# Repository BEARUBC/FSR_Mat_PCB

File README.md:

# FSR Matrix Printed Circuit Board

**As of 2023-03-24, this README is outdated. Documentation for Tiaan's FSR is in progress. 

<p align="center">
These are the CAD files for the FSR printed circuit boards (PCB) using through-hole only components. This board is used for controlling a force sensitive resistor matrix, reading analog values from each cell.  
</p>

## 📖 Description

This design is based off of Sensitronics' MatrixArray products which are comprised of a multitude of force sensing resistor elements arranged in a grid.
Providing n-input multitouch + force sensing capabilities, MatrixArrays are the basis for musical instruments, PC input devices, and other innovative designs.
If you have measured single-element FSRs by looking at the voltage across a divider, we're doing the same thing here.

But in this case, we're choosing the point to measure by powering a single drive column, enabling one mux channel so that the ADC sees a single row.
In the next section, the Arduino code demonstrates a scan pattern to read all $\approx$ 160 elements in sequence.

### 🚨 Dependencies

* Software
  * KiCAD v6
* Hardware
  * ThruMode MatrixArray
  * Arduino Uno (or other)
  * 74HC595 Shift Register (x2)
  * 74HC4051 Analog Multiplexer (x2)
  * 20k resistor (x1)
  * Solderless Breadboard & Jumper Wire

### 💻 Installing

#### 🕹️ Software

Use a web browser to navigate to www.kicad.org the KiCad EDA website. Click the DOWNLOAD button on the KiCad home page. On the download page that opens, click the Windows button. Under Stable Release, click either Windows 64-bit or Windows 32-bit, depending on if you are going to install KiCad on a 32-bit or 64-bit version of the Windows operating system. Save the KiCad installation file. It may take a while to download, depending on your internet speed.

1. Click the Open button under File > Open (`Ctrl + O`) and navigate to this repository
2. Select the `force_sens_resistor.kicad_pro` file
3. Double click the `*.sch` file and begin to edit the board

#### 🤖 Hardware

Arrange the hardware connections folling this schematic:

### ▶️ Executing program

Now that the hardware's connected, it's time to write some code.

To read a single intersection, or "cell", of the MatrixArray, we need to perform the following sequence:

* Drive the cell's row with +5V
* Enable the cell's column (multiplexer channel)
* Take an ADC reading on pin A0
* Output the reading via serial port

Simple enough, so from here, we will write a scan pattern to efficiently drive and read each cell of the Matrix. Recalling that we're calling shift register drive pins "rows" and multiplexed read pins "columns" in this example, we'll enable each column in order, and while each column is active, we'll drive each row high and take a reading.

```cpp
// Constant definitions
...

void setup() {
  Serial.begin(BAUD_RATE);

  pinMode(PIN_ADC_INPUT, INPUT);
  pinMode(PIN_SHIFT_REGISTER_DATA, OUTPUT);
  pinMode(PIN_SHIFT_REGISTER_CLOCK, OUTPUT);
  pinMode(PIN_MUX_CHANNEL_0, OUTPUT);
  pinMode(PIN_MUX_CHANNEL_1, OUTPUT);
  pinMode(PIN_MUX_CHANNEL_2, OUTPUT);
  pinMode(PIN_MUX_INHIBIT_0, OUTPUT);
  pinMode(PIN_MUX_INHIBIT_1, OUTPUT);
}
void loop() {
  for(int i = 0; i < ROW_COUNT; i ++) {
    setRow(i);
    shiftColumn(true);
    shiftColumn(false);                         //with SR clks tied, latched outputs are one clock behind

    for(int j = 0; j < COLUMN_COUNT; j ++) {
      int raw_reading = analogRead(PIN_ADC_INPUT);
      byte send_reading = (byte) (lowByte(raw_reading >> 2));
      shiftColumn(false);
      printFixed(send_reading);
      Serial.print(" ");
    }
    Serial.println();
  }
  Serial.println();
  delay(200);
}

...

// Function implementations for `setRow`, `shiftCoumn`, and `printFixed`

```

## 🧔🏽‍♂️Authors

Contributors names and contact info

Tiaan Boshoff
Kyle Kochi
Tiffany Prayitino
Umar Ali  

## 🧾 Version History

* 1.0
    * Initial Release following Sensitronics' MatrixArray tutorial

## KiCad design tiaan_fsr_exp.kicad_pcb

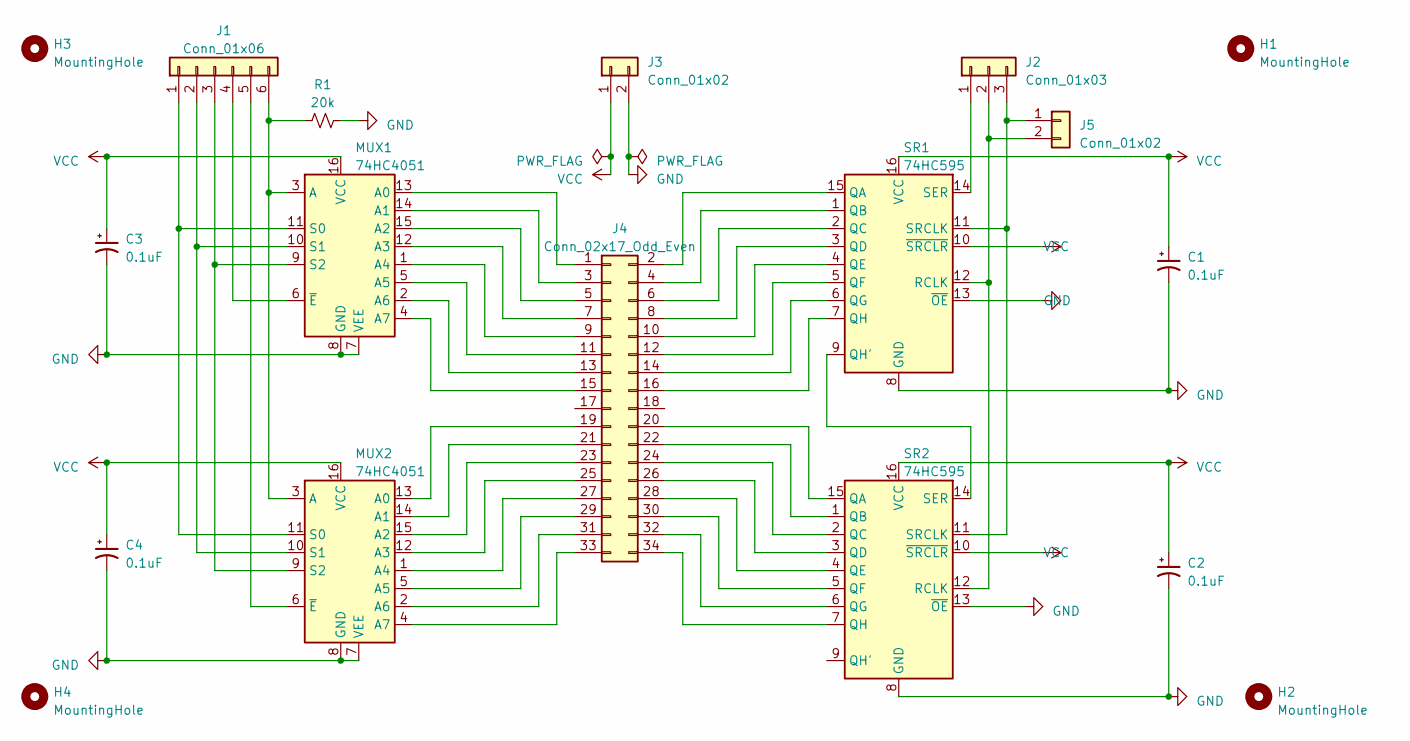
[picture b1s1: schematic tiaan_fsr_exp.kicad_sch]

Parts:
C1, C2, C3, C4: 0.1uF; CP_Radial_D4.0mm_P2.00mm
H1, H2, H3, H4: MountingHole; MountingHole_2.7mm_M2.5_DIN965_Pad
J1: Conn_01x06; JST_XH_S6B-XH-A-1_1x06_P2.50mm_Horizontal
J2: Conn_01x03; JST_XH_S3B-XH-A-1_1x03_P2.50mm_Horizontal
J3, J5: Conn_01x02; PinHeader_1x02_P2.54mm_Vertical
J4: Conn_02x17_Odd_Even; IDC-Header_2x17_P2.54mm_Vertical
MUX1, MUX2: 74HC4051; DIP-16_W7.62mm_Socket
R1: 20k; R_Axial_DIN0207_L6.3mm_D2.5mm_P10.16mm_Horizontal
SR1, SR2: 74HC595; DIP-16_W7.62mm_Socket

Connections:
GND: C1.2, C2.2, C3.2, C4.2, J3.2, MUX1.7 (VEE), MUX1.8 (GND), MUX2.7 (VEE), MUX2.8 (GND), R1.2, SR1.8 (GND), SR1.13 (~OE), SR2.8 (GND), SR2.13 (~OE)
unnamed: J1.1, MUX1.11 (S0), MUX2.11 (S0)
unnamed: J1.2, MUX1.10 (S1), MUX2.10 (S1)
unnamed: J1.3, MUX1.9 (S2), MUX2.9 (S2)
unnamed: J1.4, MUX1.6 (~E)
unnamed: J1.5, MUX2.6 (~E)
unnamed: J1.6, MUX1.3 (A), MUX2.3 (A), R1.1
unnamed: J2.1, SR1.14 (SER)
unnamed: J2.2, J5.2, SR1.12 (RCLK), SR2.12 (RCLK)
unnamed: J2.3, J5.1, SR1.11 (SRCLK), SR2.11 (SRCLK)
unnamed: J4.1, MUX1.13 (A0)
unnamed: J4.2, SR1.15 (QA)
unnamed: J4.3, MUX1.14 (A1)
unnamed: J4.4, SR1.1 (QB)
unnamed: J4.5, MUX1.15 (A2)
unnamed: J4.6, SR1.2 (QC)
unnamed: J4.7, MUX1.12 (A3)
unnamed: J4.8, SR1.3 (QD)
unnamed: J4.9, MUX1.1 (A4)
unnamed: J4.10, SR1.4 (QE)
unnamed: J4.11, MUX1.5 (A5)
unnamed: J4.12, SR1.5 (QF)
unnamed: J4.13, MUX1.2 (A6)
unnamed: J4.14, SR1.6 (QG)
unnamed: J4.15, MUX1.4 (A7)
unnamed: J4.16, SR1.7 (QH)
unnamed: J4.19, MUX2.13 (A0)
unnamed: J4.20, SR2.15 (QA)
unnamed: J4.21, MUX2.14 (A1)
unnamed: J4.22, SR2.1 (QB)
unnamed: J4.23, MUX2.15 (A2)
unnamed: J4.24, SR2.2 (QC)
unnamed: J4.25, MUX2.12 (A3)
unnamed: J4.26, SR2.3 (QD)
unnamed: J4.27, MUX2.1 (A4)
unnamed: J4.28, SR2.4 (QE)
unnamed: J4.29, MUX2.5 (A5)
unnamed: J4.30, SR2.5 (QF)
unnamed: J4.31, MUX2.2 (A6)
unnamed: J4.32, SR2.6 (QG)
unnamed: J4.33, MUX2.4 (A7)
unnamed: J4.34, SR2.7 (QH)
unnamed: SR1.9 (QH'), SR2.14 (SER)
VCC: C1.1, C2.1, C3.1, C4.1, J3.1, MUX1.16 (VCC), MUX2.16 (VCC), SR1.10 (~SRCLR), SR1.16 (VCC), SR2.10 (~SRCLR), SR2.16 (VCC)

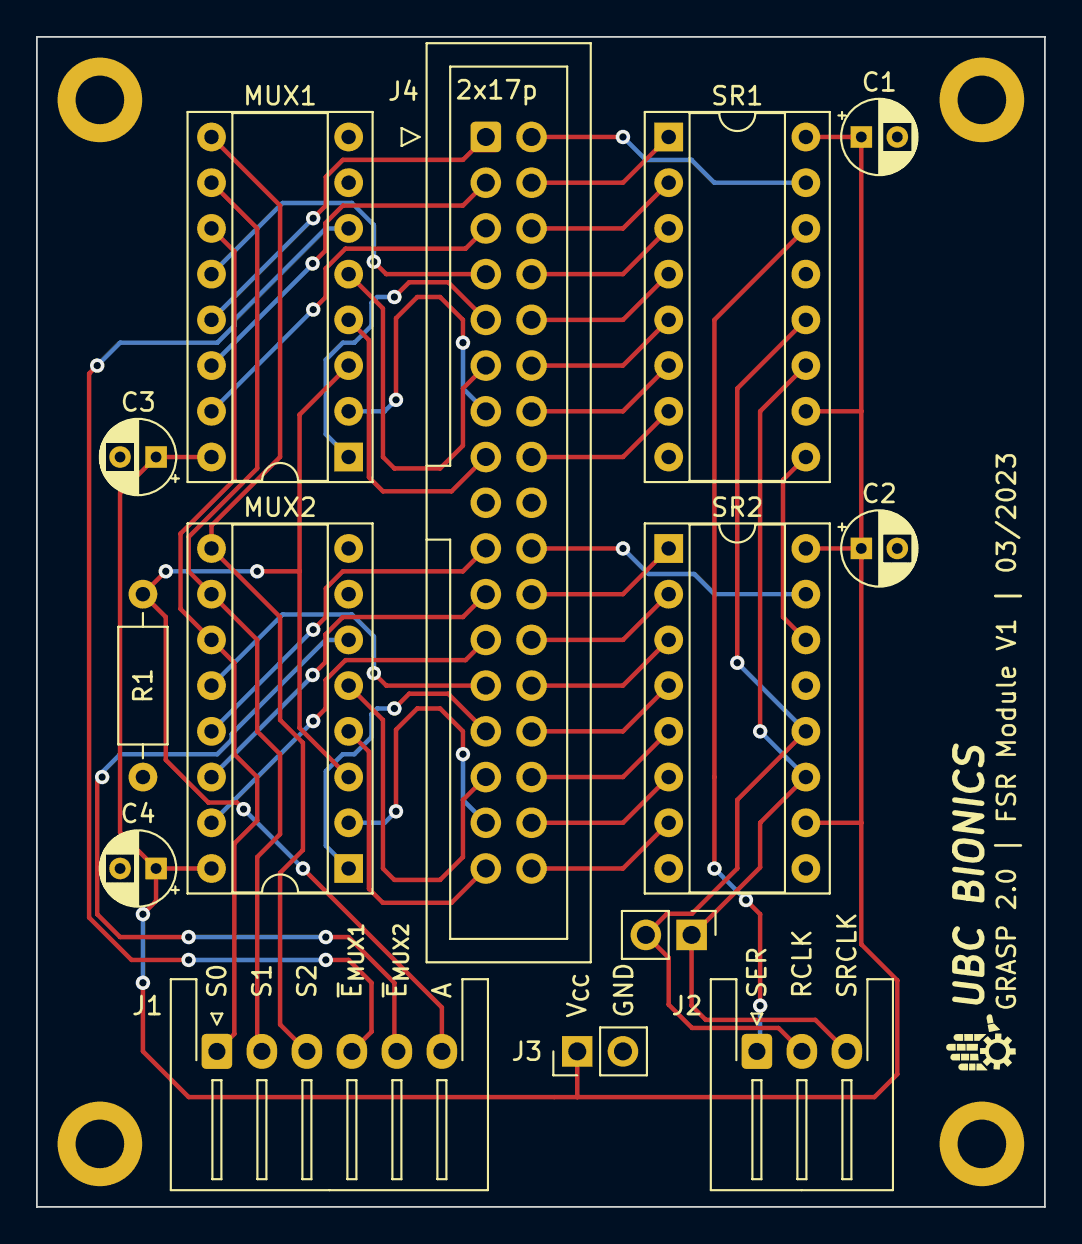
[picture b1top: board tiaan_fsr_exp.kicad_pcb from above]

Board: 2 copper layers, 56.0 x 65.0 mm, 18 parts (0 on the bottom side), 44 nets.

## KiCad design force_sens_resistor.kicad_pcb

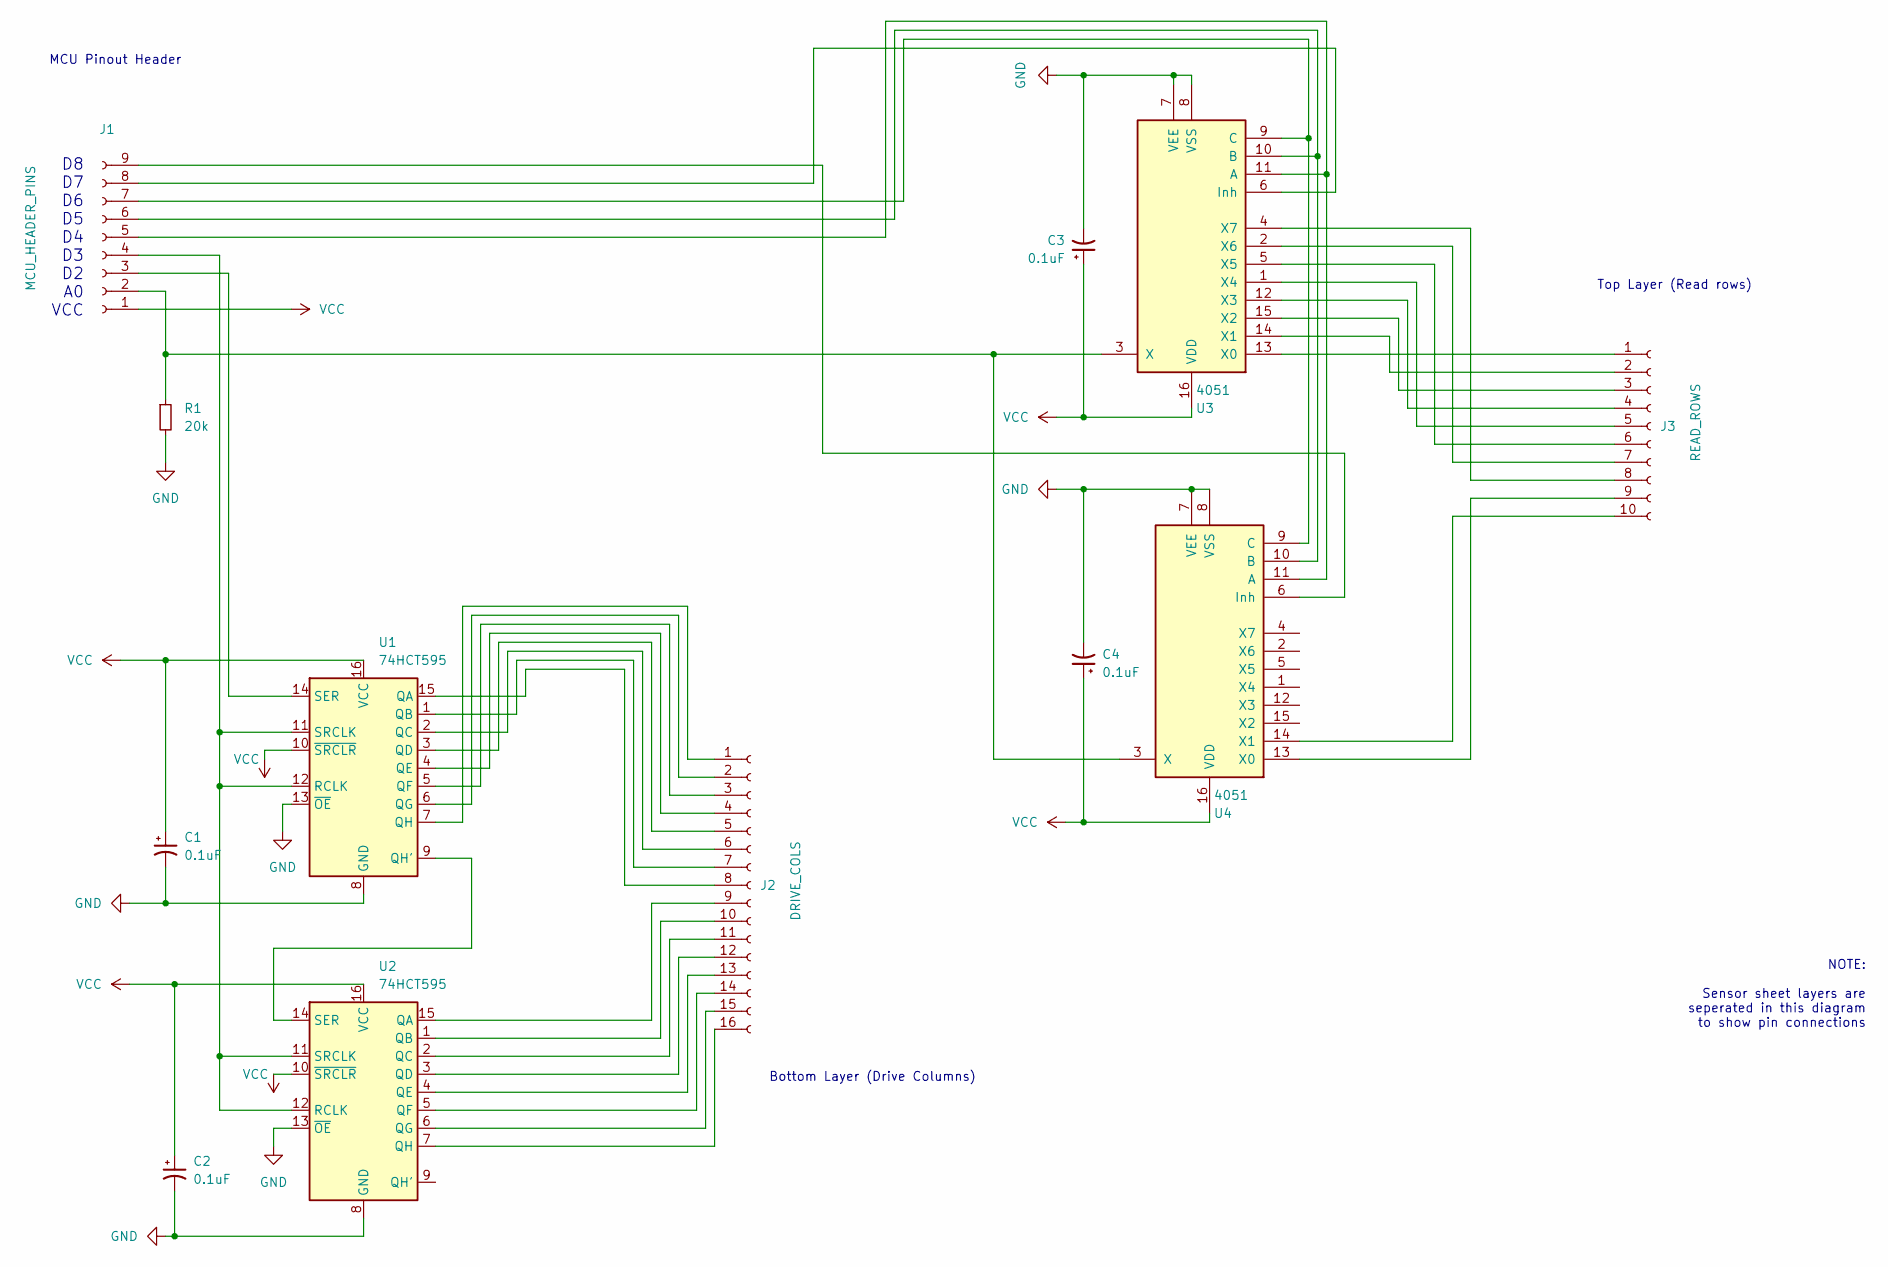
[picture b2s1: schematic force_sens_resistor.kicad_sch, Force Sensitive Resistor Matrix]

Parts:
C1, C2, C3, C4: 0.1uF; CP_Axial_L10.0mm_D4.5mm_P15.00mm_Horizontal
J1: MCU_HEADER_PINS; PinSocket_1x09_P1.00mm_Vertical
J2: DRIVE_COLS; PinSocket_1x16_P1.00mm_Vertical
J3: READ_ROWS; PinSocket_1x10_P1.00mm_Vertical
R1: 20k; R_Axial_DIN0204_L3.6mm_D1.6mm_P1.90mm_Vertical
U1, U2: 74HCT595; DIP-16_W7.62mm_LongPads
U3, U4: 4051; DIP-16_W10.16mm

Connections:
GND: C1.2, C2.2, C3.2, C4.2, R1.2, U1.8 (GND), U1.13 (~OE), U2.8 (GND), U2.13 (~OE), U3.7 (VEE), U3.8 (VSS), U4.7 (VEE), U4.8 (VSS)
unnamed: J1.2, R1.1, U3.3 (X), U4.3 (X)
unnamed: J1.3, U1.14 (SER)
unnamed: J1.4, U1.11 (SRCLK), U1.12 (RCLK), U2.11 (SRCLK), U2.12 (RCLK)
unnamed: J1.5, U3.11 (A), U4.11 (A)
unnamed: J1.6, U3.10 (B), U4.10 (B)
unnamed: J1.7, U3.9 (C), U4.9 (C)
unnamed: J1.8, U3.6 (Inh)
unnamed: J1.9, U4.6 (Inh)
unnamed: J2.1, U1.7 (QH)
unnamed: J2.2, U1.6 (QG)
unnamed: J2.3, U1.5 (QF)
unnamed: J2.4, U1.4 (QE)
unnamed: J2.5, U1.3 (QD)
unnamed: J2.6, U1.2 (QC)
unnamed: J2.7, U1.1 (QB)
unnamed: J2.8, U1.15 (QA)
unnamed: J2.9, U2.15 (QA)
unnamed: J2.10, U2.1 (QB)
unnamed: J2.11, U2.2 (QC)
unnamed: J2.12, U2.3 (QD)
unnamed: J2.13, U2.4 (QE)
unnamed: J2.14, U2.5 (QF)
unnamed: J2.15, U2.6 (QG)
unnamed: J2.16, U2.7 (QH)
unnamed: J3.1, U3.13 (X0)
unnamed: J3.2, U3.14 (X1)
unnamed: J3.3, U3.15 (X2)
unnamed: J3.4, U3.12 (X3)
unnamed: J3.5, U3.1 (X4)
unnamed: J3.6, U3.5 (X5)
unnamed: J3.7, U3.2 (X6)
unnamed: J3.8, U3.4 (X7)
unnamed: J3.9, U4.13 (X0)
unnamed: J3.10, U4.14 (X1)
unnamed: U1.9 (QH'), U2.14 (SER)
VCC: C1.1, C2.1, C3.1, C4.1, J1.1, U1.10 (~SRCLR), U1.16 (VCC), U2.10 (~SRCLR), U2.16 (VCC), U3.16 (VDD), U4.16 (VDD)

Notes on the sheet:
D8 D7 D6 D5 D4 D3 D2 A0 VCC
Bottom Layer (Drive Columns)
MCU Pinout Header
NOTE: Sensor sheet layers are seperated in this diagram to show pin connections
Top Layer (Read rows)

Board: 2 copper layers, 12 parts (0 on the bottom side), 37 nets, no tracks yet.

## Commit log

2022-11-28 Add initial CAD files for FSR
2023-03-25 Added Tiaan's FSR v1
